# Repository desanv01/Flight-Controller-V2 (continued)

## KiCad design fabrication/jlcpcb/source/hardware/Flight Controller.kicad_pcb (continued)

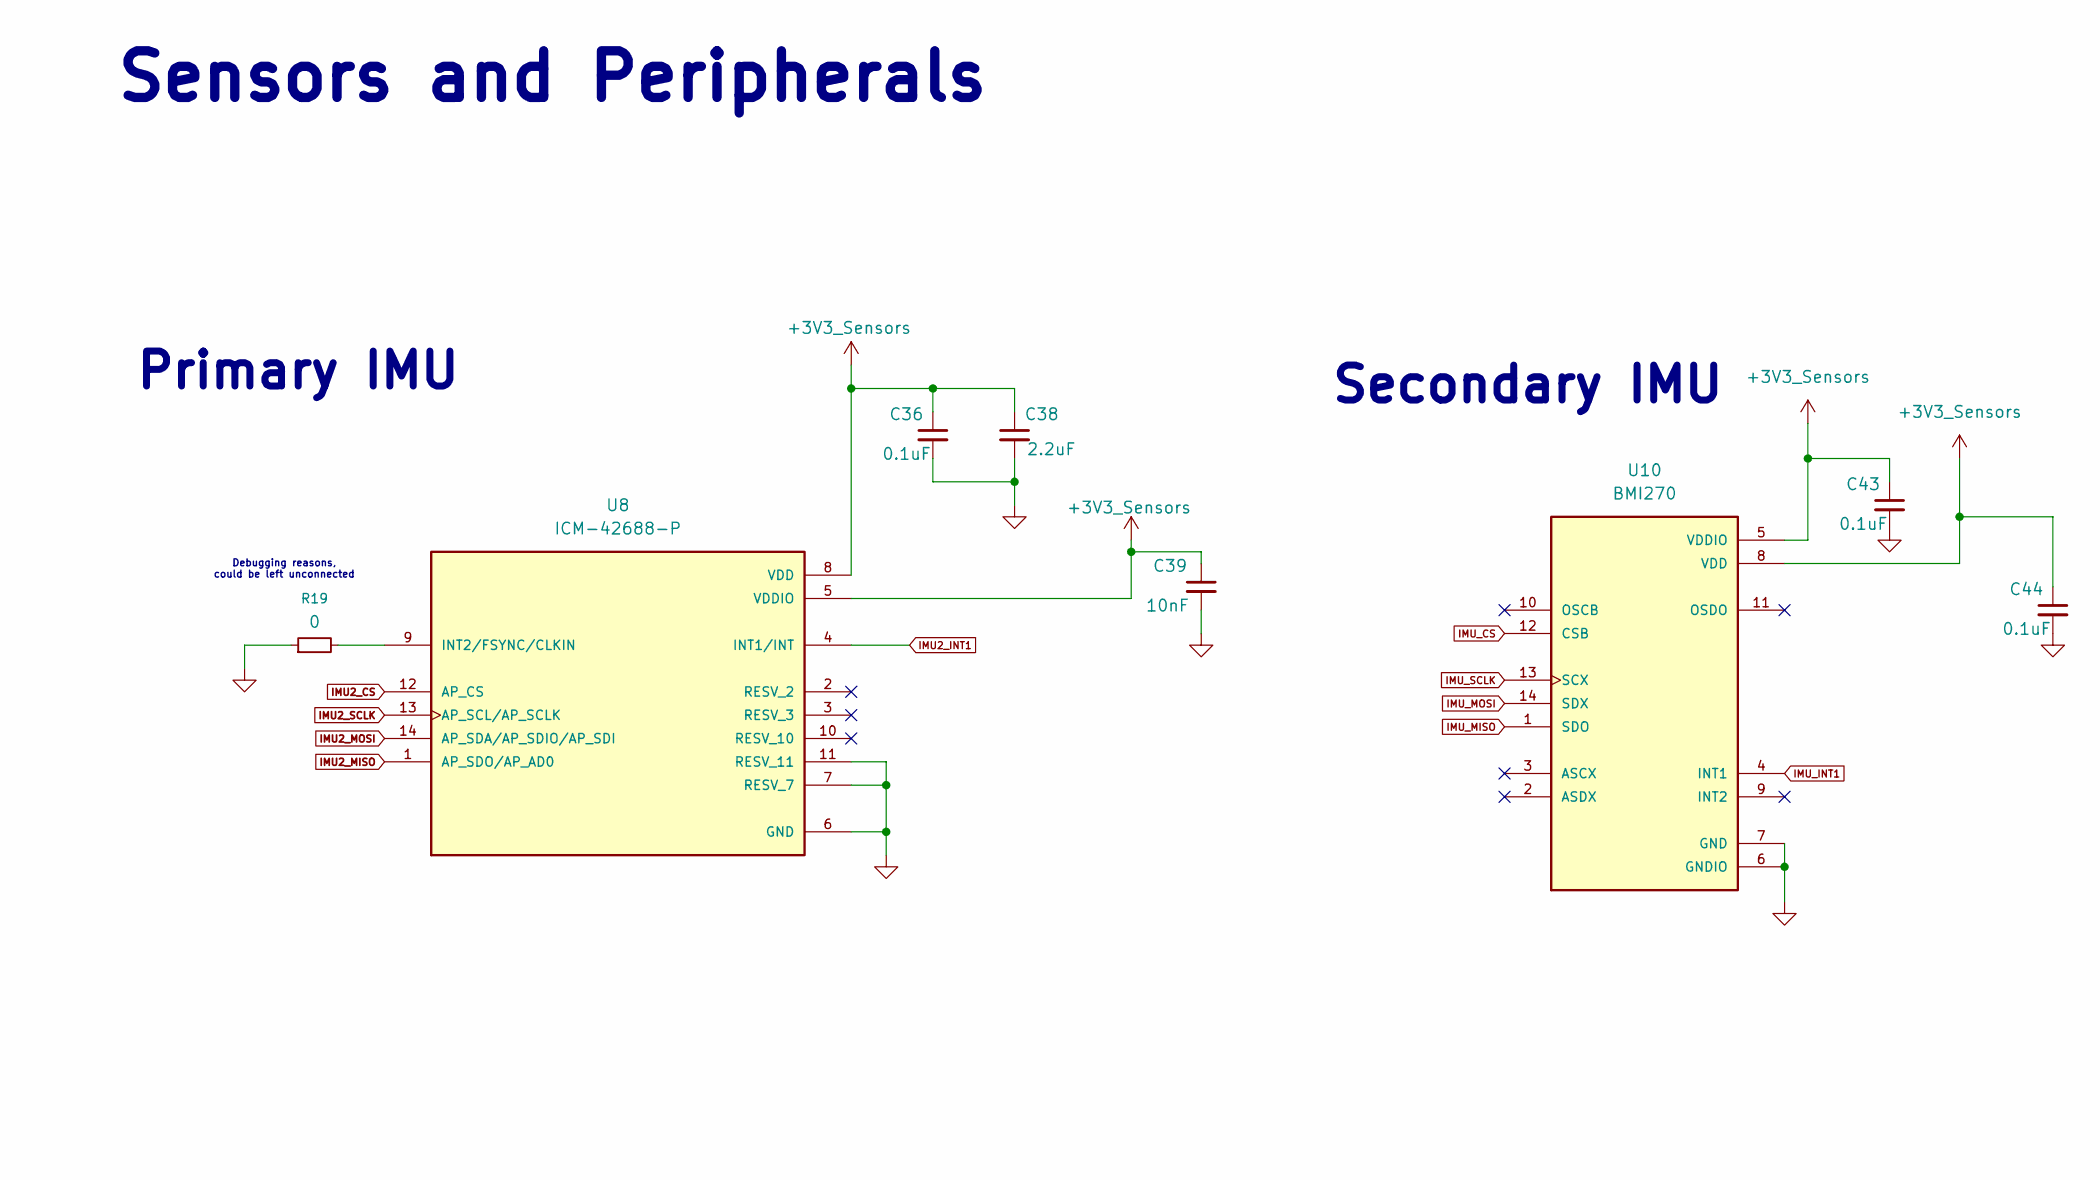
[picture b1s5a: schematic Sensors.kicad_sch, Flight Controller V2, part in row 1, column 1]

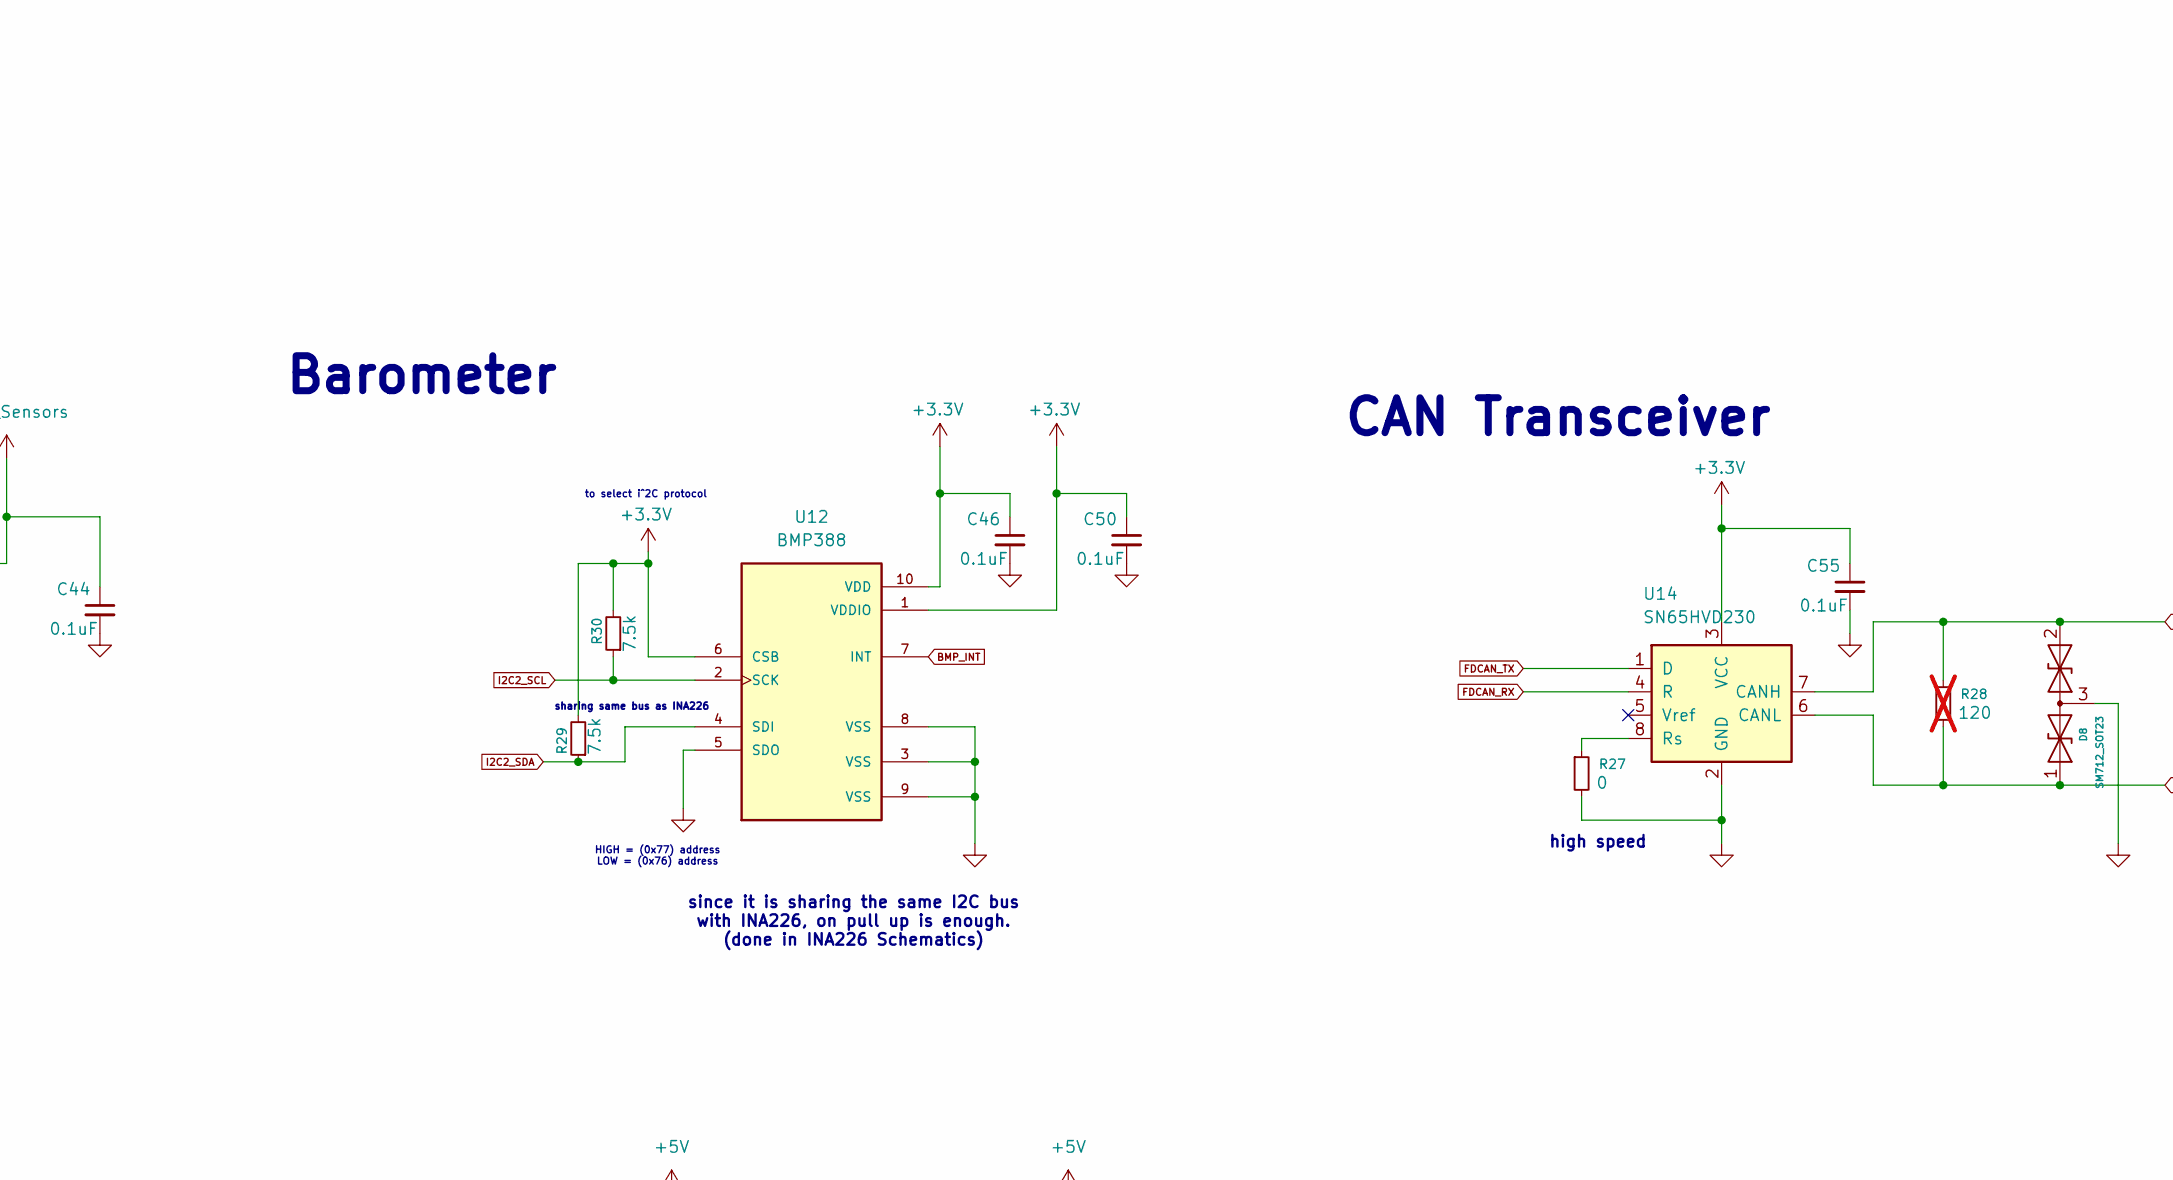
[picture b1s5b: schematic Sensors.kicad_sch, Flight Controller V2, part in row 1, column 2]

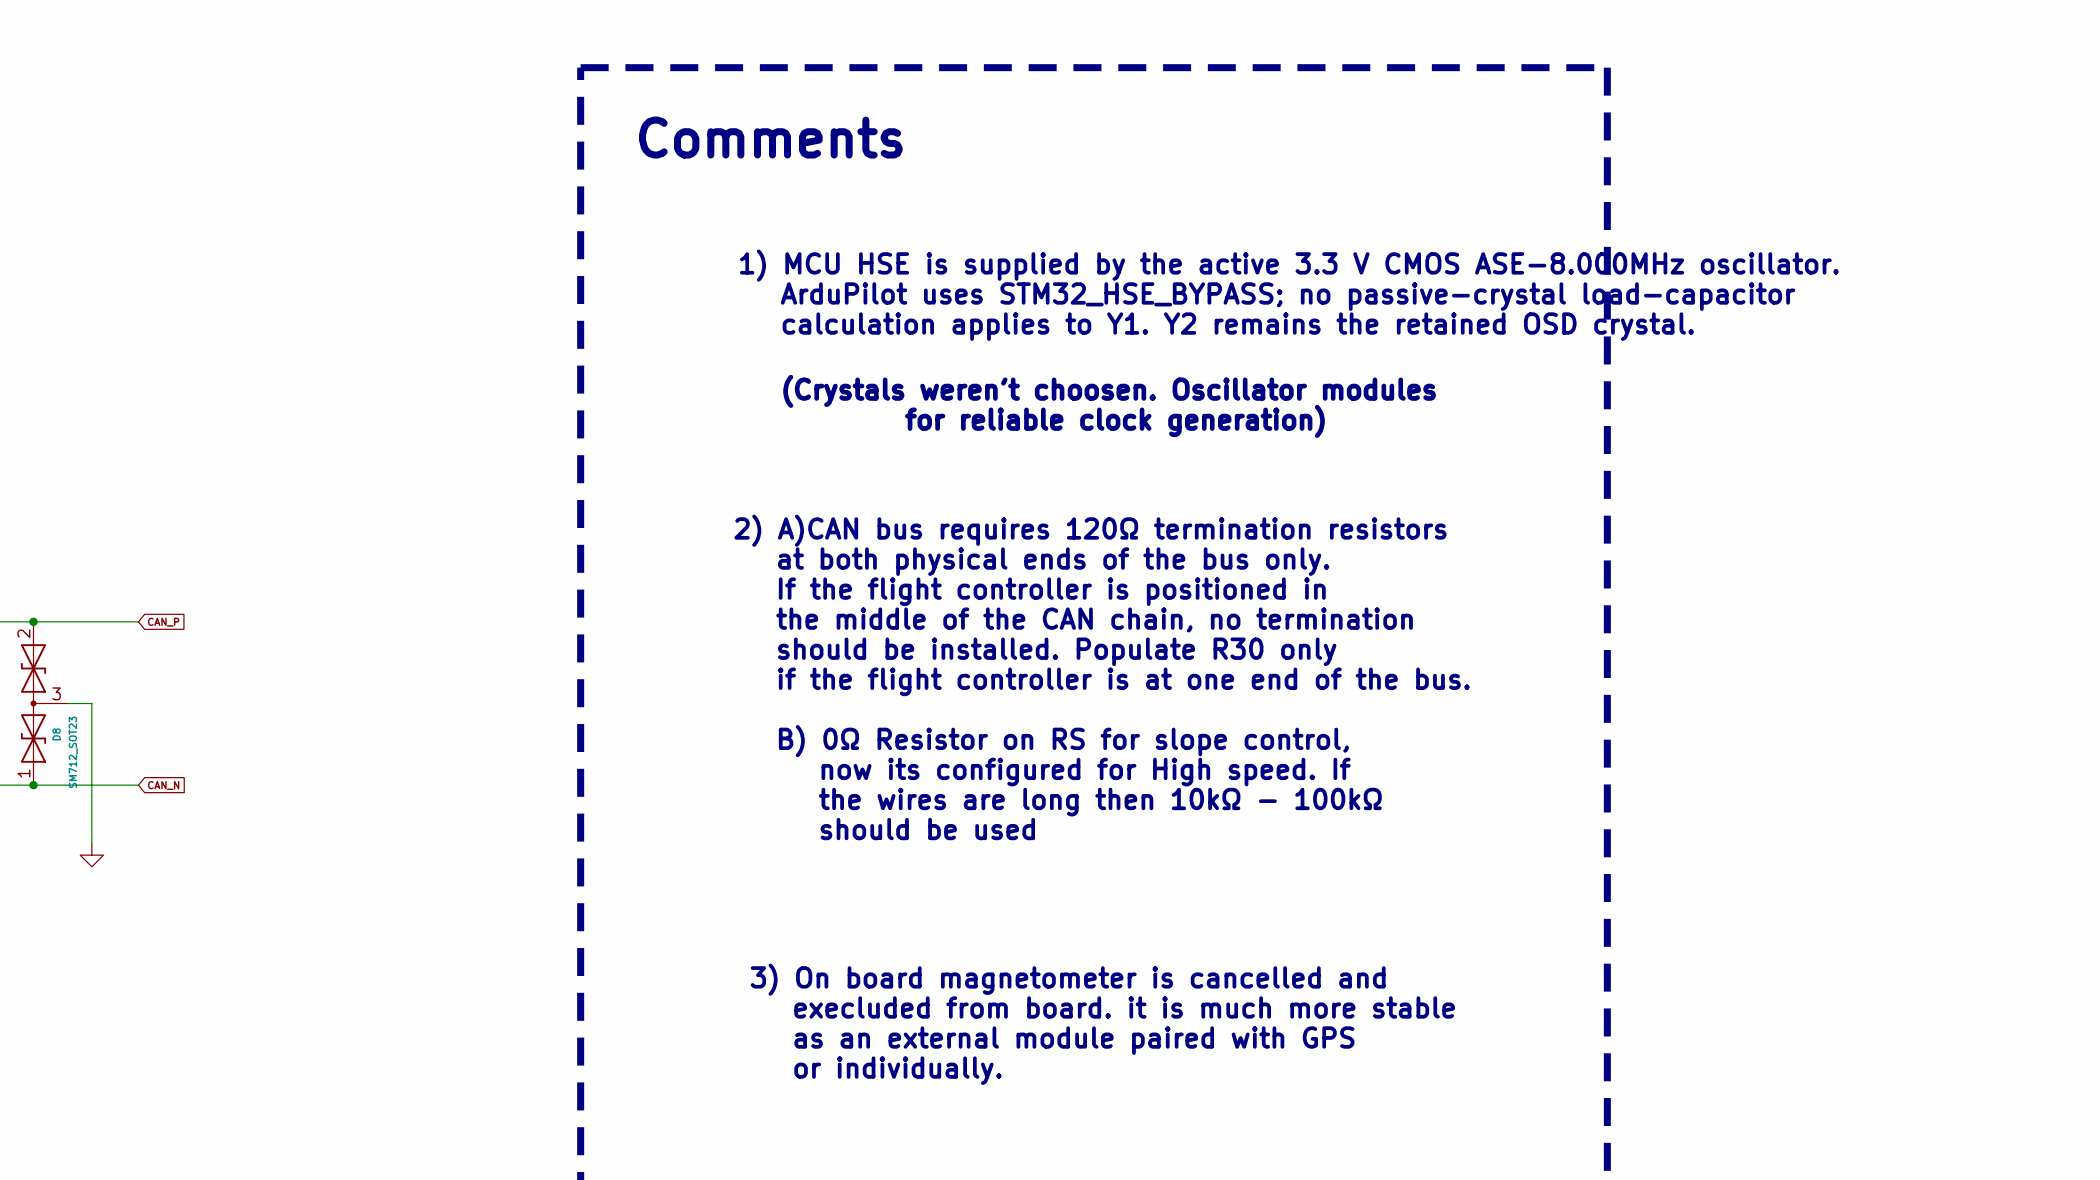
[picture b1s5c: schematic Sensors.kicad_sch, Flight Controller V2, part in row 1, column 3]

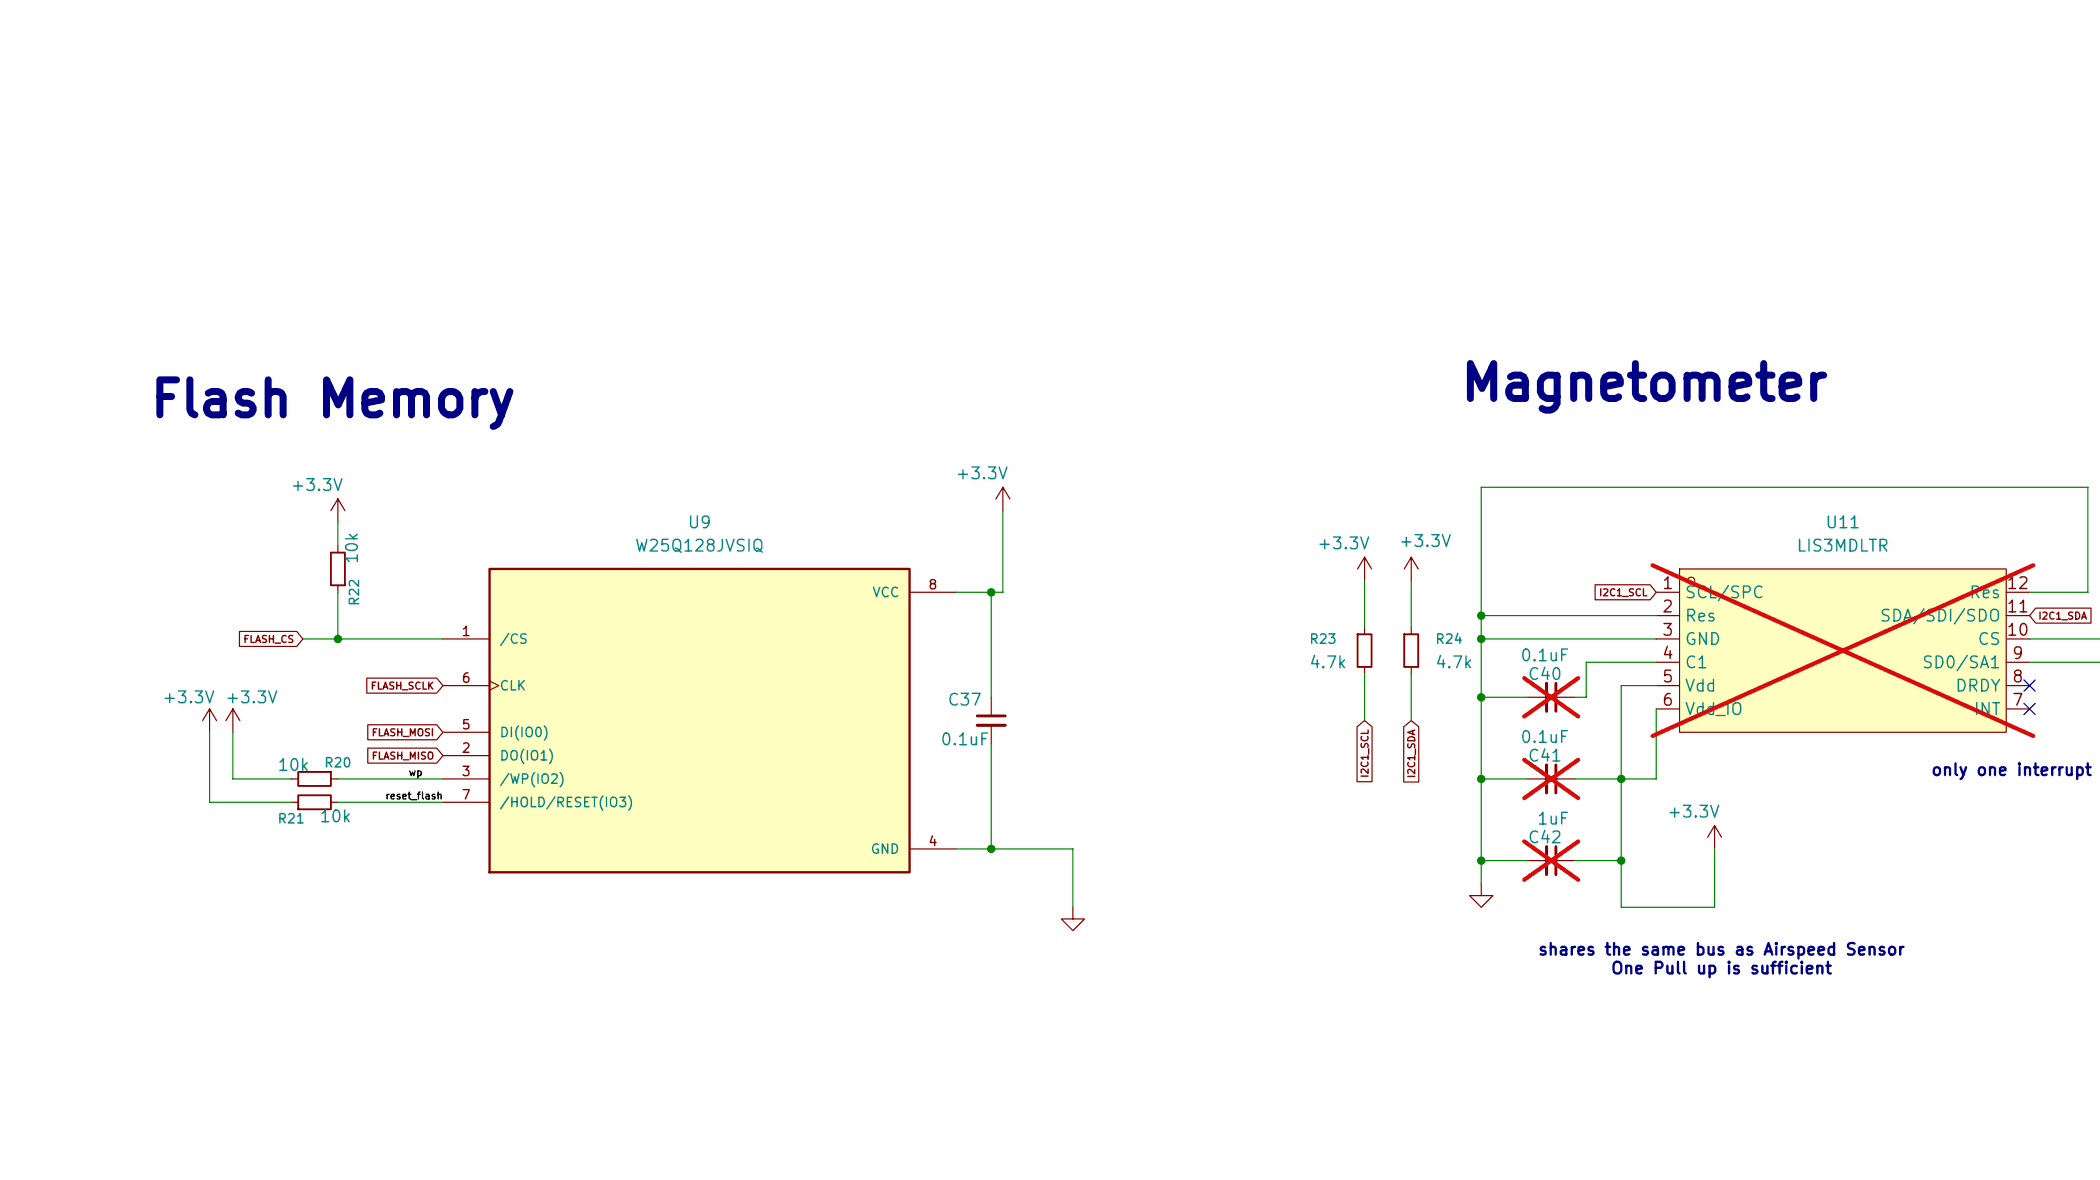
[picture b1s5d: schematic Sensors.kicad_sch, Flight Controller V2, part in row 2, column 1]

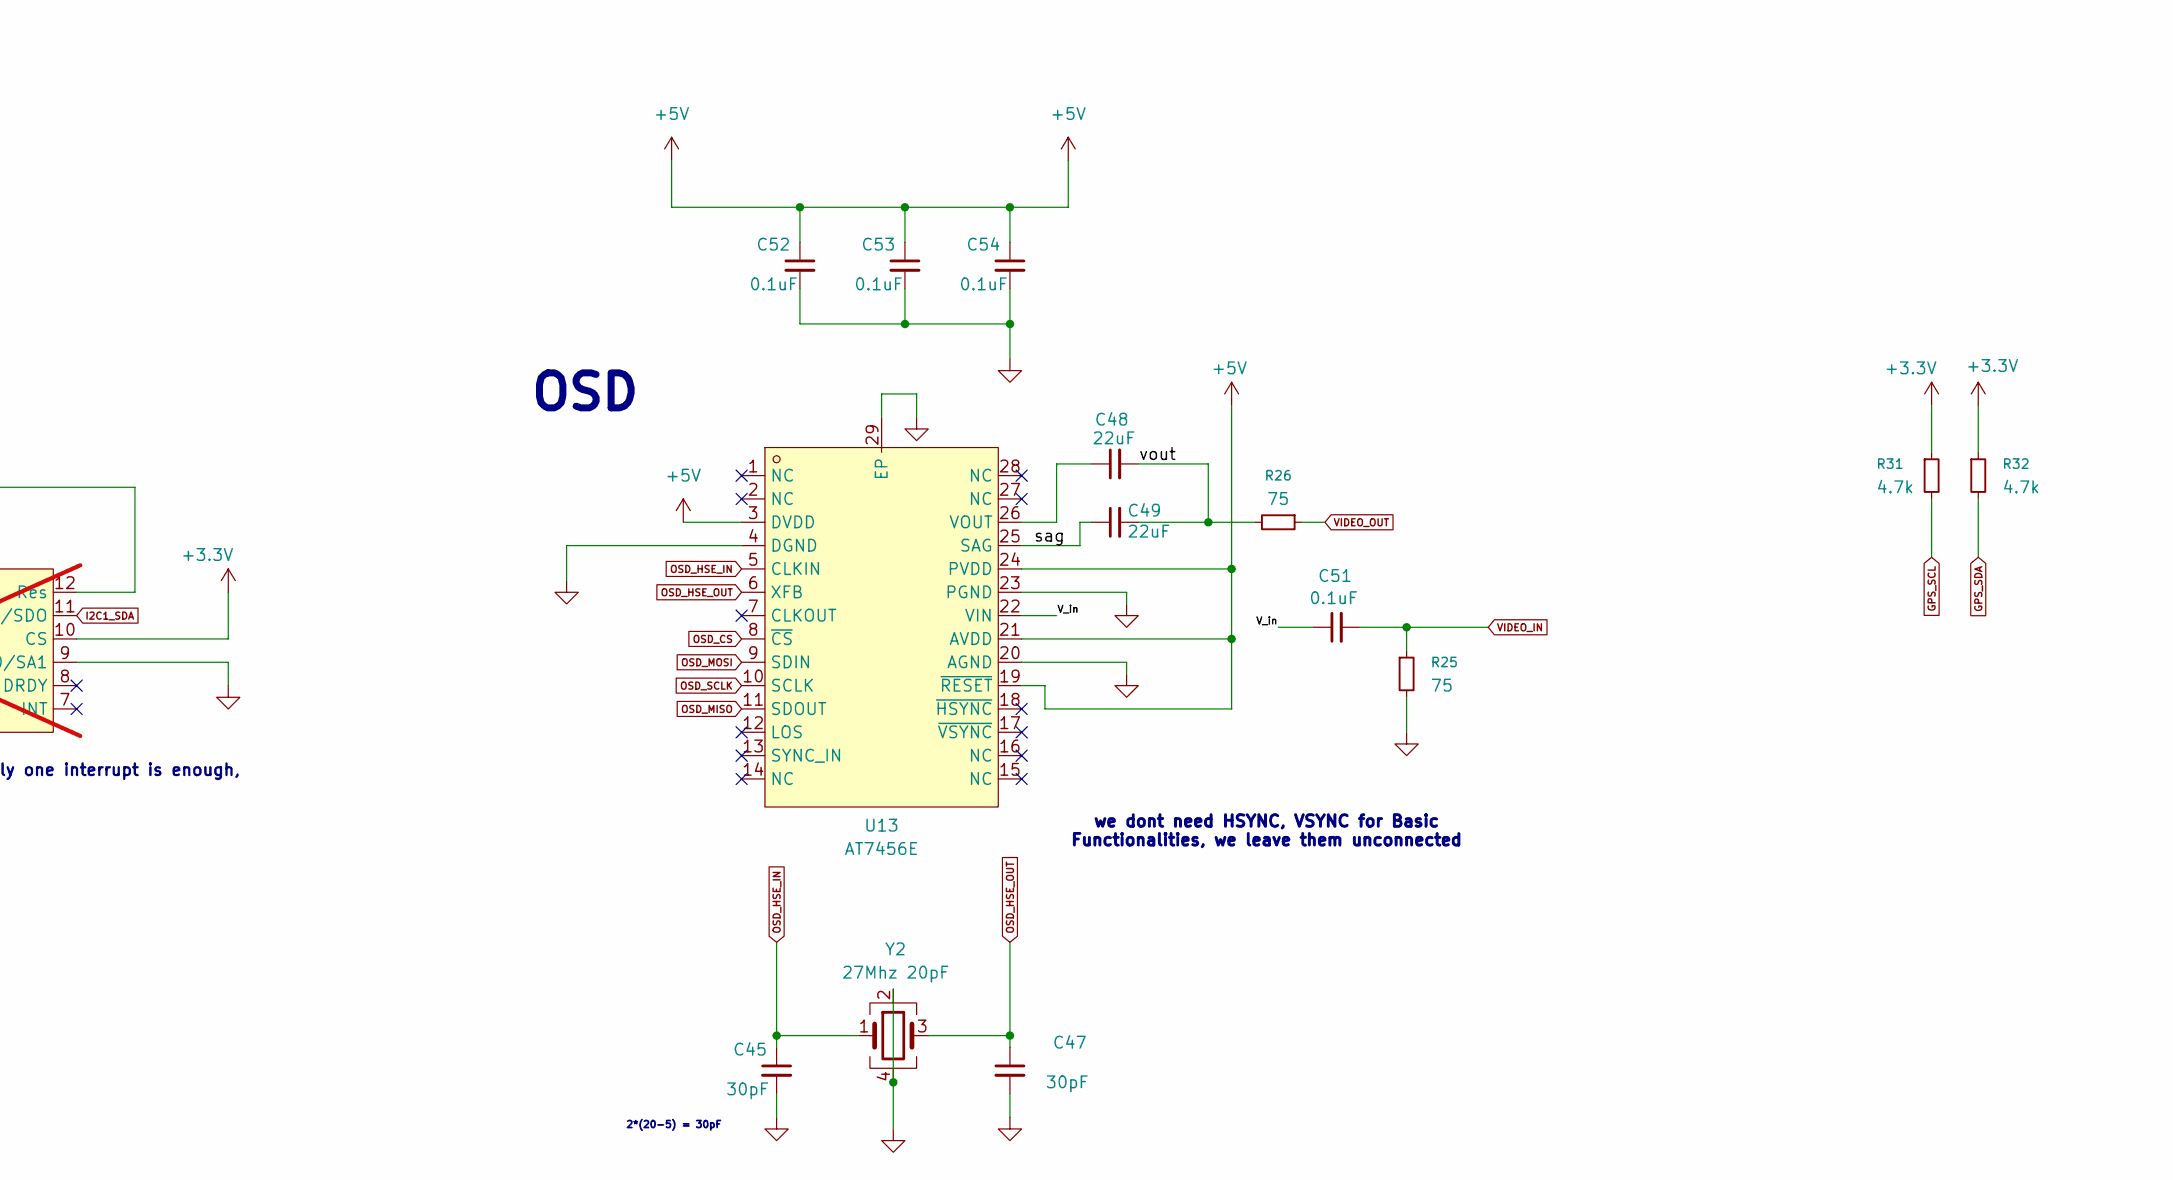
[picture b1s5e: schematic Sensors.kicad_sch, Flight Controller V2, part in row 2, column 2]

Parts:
C36, C37, C43, C44, C46, C50, C51, C52, C53, C54, C55: 0.1uF; C_0402_1005Metric
C38: 2.2uF; C_0603_1608Metric
C39: 10nF; C_0402_1005Metric
C40, C41: 0.1uF; C_0402_1005Metric; not fitted
C42: 1uF; C_0402_1005Metric; not fitted
C45, C47: 30pF; C_0402_1005Metric
C48, C49: 22uF; C_0603_1608Metric
D8: SM712_SOT23; SOT-23
R19, R27: 0; R_0402_1005Metric
R20, R21, R22: 10k; R_0402_1005Metric
R23, R24, R31, R32: 4.7k; R_0402_1005Metric
R25, R26: 75; R_0402_1005Metric
R28: 120; R_0402_1005Metric; not fitted
R29, R30: 7.5k; R_0402_1005Metric
U8: ICM-42688-P; PQFN50P300X250X97-14N; PARTREV 1.2
U9: W25Q128JVSIQ; PARTREV I
U10: BMI270; XDCR_BMI270
U11: LIS3MDLTR; (mag)LGA-12_L2.0-W2.0-P0.50-BL; LCSC Part C478483; not fitted
U12: BMP388; PQFN50P200X200X80-10N; PARTREV 1.1
U13: AT7456E; LCSC Part C82351
U14: SN65HVD230; SOIC-8_3.9x4.9mm_P1.27mm
Y2: 27Mhz 20pF; Crystal_SMD_3225-4Pin_3.2x2.5mm

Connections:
+3.3V: C37.1, C41.1, C42.1, C46.1, C50.1, C55.1, R20.2, R21.1, R22.2, R23.1, R24.1, R29.2, R30.2, R31.1, R32.1, U9.8 (VCC), U11.5 (Vdd), U11.6 (Vdd_IO), U11.10 (CS), U12.1 (VDDIO), U12.6 (CSB), U12.10 (VDD), U14.3 (VCC); also elsewhere on the board
+3V3_Sensors: C36.1, C38.1, C39.1, C43.1, C44.1, U8.5 (VDDIO), U8.8 (VDD), U10.5 (VDDIO), U10.8 (VDD); also elsewhere on the board
+5V: C52.1, C53.1, C54.1, U13.3 (DVDD), U13.19 (~RESET), U13.21 (AVDD), U13.24 (PVDD); also elsewhere on the board
/Sensors and Peripherals/V_in: C51.1, U13.22 (VIN)
/Sensors and Peripherals/reset_flash: R21.2, U9.7 (/HOLD/RESET(IO3))
/Sensors and Peripherals/sag: C49.1, U13.25 (SAG)
/Sensors and Peripherals/vout: C48.2, C49.2, R26.2
/Sensors and Peripherals/wp: R20.1, U9.3 (/WP(IO2))
BMP_INT: U12.7 (INT); also elsewhere on the board
CAN_N: D8.1 (A1), R28.2, U14.6 (CANL); also elsewhere on the board
CAN_P: D8.2 (A2), R28.1, U14.7 (CANH); also elsewhere on the board
FDCAN_RX: U14.4 (R); also elsewhere on the board
FDCAN_TX: U14.1 (D); also elsewhere on the board
FLASH_CS: R22.1, U9.1 (/CS); also elsewhere on the board
FLASH_MISO: U9.2 (DO(IO1)); also elsewhere on the board
FLASH_MOSI: U9.5 (DI(IO0)); also elsewhere on the board
FLASH_SCLK: U9.6 (CLK); also elsewhere on the board
GND: C36.2, C37.2, C38.2, C39.2, C40.2, C41.2, C42.2, C43.2, C44.2, C45.2, C46.2, C47.2, C50.2, C52.2, C53.2, C54.2, C55.2, D8.3 (common), R19.1, R25.2, R27.2, U8.6 (GND), U8.7 (RESV_7), U8.11 (RESV_11), U9.4 (GND), U10.6 (GNDIO), U10.7 (GND), U11.2 (Res), U11.3 (GND), U11.9 (SD0/SA1), U11.12 (Res), U12.3 (VSS), U12.5 (SDO), U12.8 (VSS), U12.9 (VSS), U13.4 (DGND), U13.20 (AGND), U13.23 (PGND), U13.29 (EP), U14.2 (GND), Y2.2, Y2.4; also elsewhere on the board
GPS_SCL: R31.2; also elsewhere on the board
GPS_SDA: R32.2; also elsewhere on the board
I2C1_SCL: R23.2, U11.1 (SCL/SPC); also elsewhere on the board
I2C1_SDA: R24.2, U11.11 (SDA/SDI/SDO); also elsewhere on the board
I2C2_SCL: R30.1, U12.2 (SCK); also elsewhere on the board
I2C2_SDA: R29.1, U12.4 (SDI); also elsewhere on the board
IMU2_CS: U8.12 (AP_CS); also elsewhere on the board
IMU2_INT1: U8.4 (INT1/INT); also elsewhere on the board
IMU2_MISO: U8.1 (AP_SDO/AP_AD0); also elsewhere on the board
IMU2_MOSI: U8.14 (AP_SDA/AP_SDIO/AP_SDI); also elsewhere on the board
IMU2_SCLK: U8.13 (AP_SCL/AP_SCLK); also elsewhere on the board
IMU_CS: U10.12 (CSB); also elsewhere on the board
IMU_INT1: U10.4 (INT1); also elsewhere on the board
IMU_MISO: U10.1 (SDO); also elsewhere on the board
IMU_MOSI: U10.14 (SDX); also elsewhere on the board
IMU_SCLK: U10.13 (SCX); also elsewhere on the board
unnamed: C40.1, U11.4 (C1)
unnamed: R19.2, U8.9 (INT2/FSYNC/CLKIN)
unnamed: C48.1, U13.26 (VOUT)
unnamed: R27.1, U14.8 (Rs)
OSD_CS: U13.8 (~CS); also elsewhere on the board
OSD_HSE_IN: C45.1, U13.5 (CLKIN), Y2.1
OSD_HSE_OUT: C47.1, U13.6 (XFB), Y2.3
OSD_MISO: U13.11 (SDOUT); also elsewhere on the board
OSD_MOSI: U13.9 (SDIN); also elsewhere on the board
OSD_SCLK: U13.10 (SCLK); also elsewhere on the board
VIDEO_IN: C51.2, R25.1; also elsewhere on the board
VIDEO_OUT: R26.1; also elsewhere on the board

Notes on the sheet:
Debugging reasons, could be left unconnected
shares the same bus as Airspeed Sensor One Pull up is sufficient
high speed
we dont need HSYNC, VSYNC for Basic Functionalities, we leave them unconnected
sharing same bus as INA226
(Crystals weren't choosen. Oscillator modules for reliable clock generation)
2*(20-5) = 30pF
1) MCU HSE is supplied by the active 3.3 V CMOS ASE-8.000MHz oscillator. ArduPilot uses STM32_HSE_BYPASS; no passive-crystal load-capacitor calculation applies to Y1. Y2 remains the retained OSD crystal.
HIGH = (0x77) address LOW = (0x76) address
to select i^2C protocol
only one interrupt is enough,
Magnetometer
2) A)CAN bus requires 120Ω termination resistors at both physical ends of the bus only. If the flight controller is positioned in the middle of the CAN chain, no termination should be installed. Populate R30 only if the flight controller is at one end of the bus. B) 0Ω Resistor on RS for slope cont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
Barometer
Flash Memory
3) On board magnetometer is cancelled and execluded from board. it is much more stable as an external module paired with GPS or individually.
OSD
Comments
Secondary IMU
Primary IMU
CAN Transceiver
Sensors and Peripherals
since it is sharing the same I2C bus with INA226, on pull up is enough. (done in INA226 Schematics)

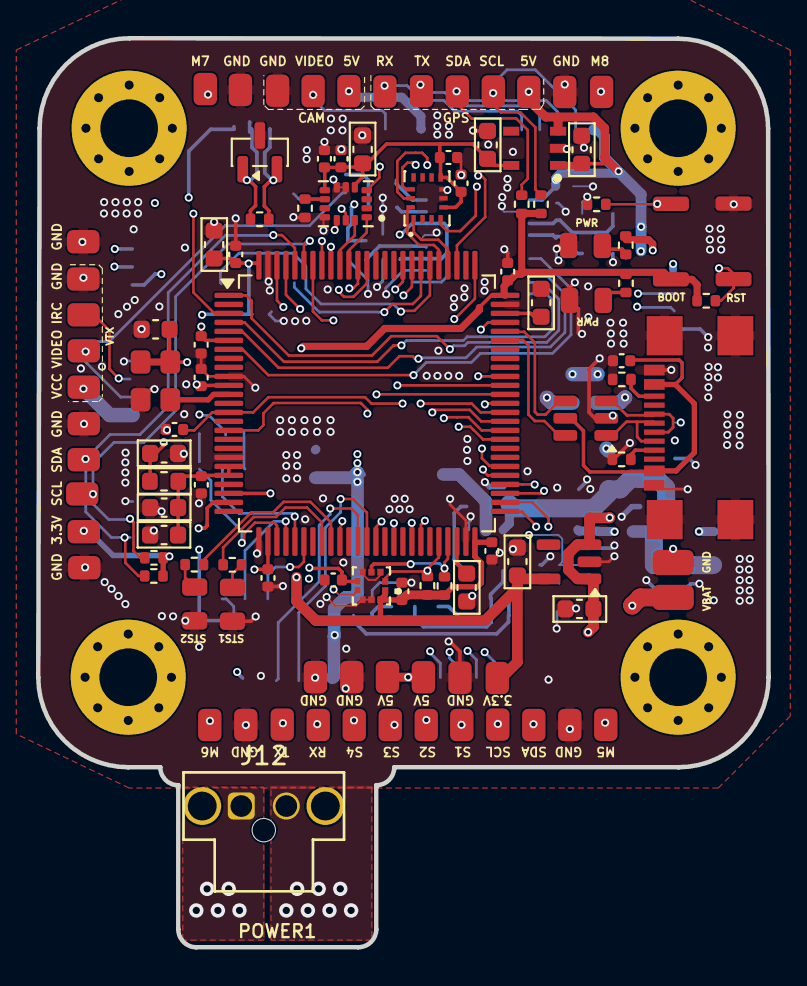
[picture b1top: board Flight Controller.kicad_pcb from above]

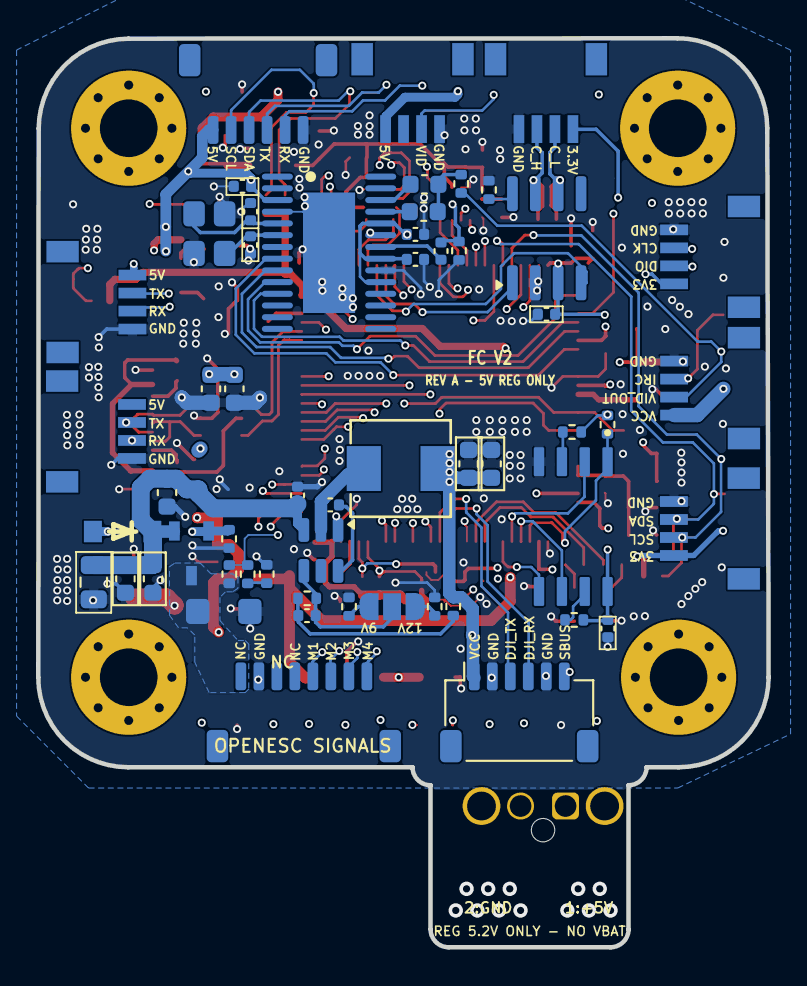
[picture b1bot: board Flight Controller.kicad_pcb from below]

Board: 6 copper layers, 40.6 x 50.5 mm, 162 parts (55 on the bottom side), 102 nets.

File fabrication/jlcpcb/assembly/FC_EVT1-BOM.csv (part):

"Designators","Value","Footprint","Datasheet","Description","Manufacturer","MPN","LCSC","MatingHousing","CrimpTerminal","TPA","Qty"
"C1,C3,C10","10uF","Capacitor_SMD:C_0603_1608Metric","","Unpolarized capacitor, small symbol","","","","","","","3"
"C2,C5,C24-C26,C28,C29,C31,C32,C36,C37,C43,C44,C46,C50-C55","0.1uF","Capacitor_SMD:C_0402_1005Metric","","Unpolarized capacitor, small symbol","","","","","","","20"
"C4","22uF","Capacitor_SMD:C_0805_2012Metric","","Unpolarized capacitor, small symbol","","","","","","","1"
"C6,C7,C15,C16,C48,C49","22uF","Capacitor_SMD:C_0603_1608Metric","","Unpolarized capacitor, small symbol","","","","","","","6"
"C8","75pF","Capacitor_SMD:C_0402_1005Metric","","Unpolarized capacitor, small symbol","","","","","","","1"
"C9","4.7uF","Capacitor_SMD:C_0402_1005Metric","","Unpolarized capacitor, small symbol","","","","","","","1"
"C17,C18,C20,C23,C27","1uF","Capacitor_SMD:C_0603_1608Metric","","Unpolarized capacitor, small symbol","","","","","","","5"
"C19,C22","4.7uF","Capacitor_SMD:C_0603_1608Metric","","Unpolarized capacitor, small symbol","","","","","","","2"
"C21","10nF","Capacitor_SMD:C_0603_1608Metric","","Unpolarized capacitor, small symbol","","","","","","","1"
"C30,C39","10nF","Capacitor_SMD:C_0402_1005Metric","","Unpolarized capacitor, small symbol","","","","","","","2"
"C33","0.1uF","Capacitor_SMD:C_0603_1608Metric","","Unpolarized capacitor, small symbol","","","","","","","1"
"C34,C35,C38","2.2uF","Capacitor_SMD:C_0603_1608Metric","","Unpolarized capacitor, small symbol","","","","","","","3"
"C45,C47","30pF","Capacitor_SMD:C_0402_1005Metric","","Unpolarized capacitor, small symbol","","","","","","","2"
"D1","SMF26A","Diode_SMD:D_SMF","https://www.vishay.com/doc?85881","200W unidirectional Transil Transient Voltage Suppressor, 26Vrwm, SMF","","","","","","","1"
"D2","BZT52C12-13-F","memo:(zener)SOD-123F_L2.8-W1.8-LS3.7-RD","https://lcsc.com/product-detail/Others_Diodes-Incorporated_B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","","","","","","","","1"
"D4-D7","LED","LED_SMD:LED_0805_2012Metric","","Light emitting diode","","","","","","","4"
"D8","SM712_SOT23","Package_TO_SOT_SMD:SOT-23","https://www.littelfuse.com/~/media/electronics/datasheets/tv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","7V/12V, 600W Asymmetrical TVS Diode Array, SOT-23","","","","","","","1"
"FB1","1k@100Mhz","Inductor_SMD:L_0603_1608Metric","","Ferrite bead, small symbol","","","","","","","1"
"H1-H4","MountingHole","MountingHole:MountingHole_3.2mm_M3_Pad_Via","","","","","","","","","4"
"J1","USB4110GFA","memo:GCT_USB4110GFA","","","","","","","","","1"
"J2","FPV","memo:CONN-SMD_4P-P1.00_SM04B-SRSS-TB-LF-SN","","","","","","","","","1"
"J3","ST_LINK","memo:CONN-SMD_4P-P1.00_SM04B-SRSS-TB-LF-SN","","Generic connector, single row, 01x04, script generated (kicad-library-utils/schlib/autogen/connector/)","","","","","","","1"
"J4","GPS","Connector_JST:JST_SH_SM06B-SRSS-TB_1x06-1MP_P1.00mm_Horizontal","","Generic connector, single row, 01x06, script generated (kicad-library-utils/schlib/autogen/connector/)","","","","","","","1"
"J5","Airspeed sensor","memo:CONN-SMD_4P-P1.00_SM04B-SRSS-TB-LF-SN","","","","","","","","","1"
"J6","OpenESC SIGNAL-ONLY","Connector_JST:JST_SH_SM08B-SRSS-TB_1x08-1MP_P1.00mm_Horizontal","","Generic connector, single row, 01x08, script generated (kicad-library-utils/schlib/autogen/connector/)","","","","","","","1"
"J7","RC Receiver","memo:CONN-SMD_4P-P1.00_SM04B-SRSS-TB-LF-SN","","Generic connector, single row, 01x04, script generated (kicad-library-utils/schlib/autogen/connector/)","","","","","","","1"
"J8","VTX","memo:CONN-SMD_4P-P1.00_SM04B-SRSS-TB-LF-SN","","","","","","","","","1"
"J9","DJI","Connector_JST:JST_SH_SM06B-SRSS-TB_1x06-1MP_P1.00mm_Horizontal","","Generic connector, single row, 01x06, script generated (kicad-library-utils/schlib/autogen/connector/)","","","","","","","1"
"J10","CAN BUS","memo:CONN-SMD_4P-P1.00_SM04B-SRSS-TB-LF-SN","","","","","","","","","1"
"J11","MAVLINK SIGNAL-ONLY","memo:CONN-SMD_4P-P1.00_SM04B-SRSS-TB-LF-SN","","","","","","","","","1"
"J12","POWER1 REGULATED 5.2V IN","FC_Footprints:Molex_Nano-Fit_105311-1202_1x02_P2.50mm_Vertical_SolderClip","https://www.molex.com/en-us/products/part-detail/1053111202","Nano-Fit 2.50 mm 2-circuit vertical top-entry solder-clip header; black; 0.38 um gold; pin 1 +5V, pin 2 GND","Molex","105311-1202","","105307-1202","105300-2200","105325-1002","1"
"L1","15uH","memo:IND-SMD_L5.4-W5.2","","Inductor, small symbol","","","","","","","1"
"Q1","AO3407A","memo:AO3407A","https://lcsc.com/product-detail/MOSFET_AOS_AO3407A_AO3407A_C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","","","","","","","","1"
"R1,R2","5.1k","Resistor_SMD:R_0402_1005Metric","","Resistor, small symbol","","","","","","","2"
"R3,R5","100k","Resistor_SMD:R_0402_1005Metric","","Resistor, small symbol","","","","","","","2"
"R4","49.9","Resistor_SMD:R_0402_1005Metric","","Resistor, small symbol","","","","","","","1"
"R5B1","7.15K","Resistor_SMD:R_0402_1005Metric","","Resistor, small symbol","","","","","","","1"
"R5C1","5.23k","Resistor_SMD:R_0402_1005Metric","","Resistor, small symbol","","","","","","","1"
"R6","4.42k","Resistor_SMD:R_0402_1005Metric","","Resistor, small symbol","","","","","","","1"
"R7","20k","Resistor_SMD:R_0402_1005Metric","","Resistor, small symbol","","","","","","","1"
"R8,R19,R27","0","Resistor_SMD:R_0402_1005Metric","","Resistor, small symbol","","","","","","","3"
"R13,R14,R17,R18","330","Resistor_SMD:R_0402_1005Metric","","Resistor, small symbol","","","","","","","4"
"R15,R16,R20-R22","10k","Resistor_SMD:R_0402_1005Metric","","Resistor, small symbol","","","","","","","5"
"R23,R24,R31,R32","4.7k","Resistor_SMD:R_0402_1005Metric","","Resistor, small symbol","","","","","","","4"
"R25,R26","75","Resistor_SMD:R_0402_1005Metric","","Resistor, small symbol","","","","","","","2"
"R29,R30","7.5k","Resistor_SMD:R_0402_1005Metric","","Resistor, small symbol","","","","","","","2"
"SW1","reset","Button_Switch_SMD:SW_Push_SPST_NO_Alps_SKRK","","Push button switch, generic, two pins","","","","","","","1"
"SW2","MCU_BOOT","Button_Switch_SMD:SW_Push_SPST_NO_Alps_SKRK","","Push button switch, generic, two pins","","","","","","","1"
"U1","TPS54302","Package_TO_SOT_SMD:SOT-23-6","http://www.ti.com/lit/ds/symlink/tps54302.pdf","3A, 4.5 to 28V Input, EMI Friendly integrated switch synchronous step-down regulator, pulse-skipping, SOT-23-6","","","","","","","1"
"U2","USBLC6-2SC6","Package_TO_SOT_SMD:SOT-23-6","https://www.st.com/resource/en/datasheet/usblc6-2.pdf","Very low capacitance ESD protection diode, 2 data-line, SOT-23-6","","","","","","","1"
"U5","AP2112K-3.3","Package_TO_SOT_SMD:SOT-23-5","https://www.diodes.com/assets/Datasheets/AP2112.pdf","600mA low dropout linear regulator, with enable pin, 3.8V-6V input voltage range, 3.3V fixed positive output, SOT-23-5","","","","","","","1"
"U6","AP7343-33W5-7","memo:(AP7343 )SOT-25_L3.0-W1.6-P0.95-LS2.8-BL","https://lcsc.com/product-detail/presales_Diodes-Incorporated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","","","","","","","","1"
"U7","STM32H743VITx","Package_QFP:LQFP-100_14x14mm_P0.5mm","https://www.st.com/resource/en/datasheet/stm32h743vi.pdf","STMicroelectronics Arm Cortex-M7 MCU, 2048KB flash, 1024KB RAM, 480 MHz, 1.71-3.6V, 82 GPIO, LQFP100","","","","","","","1"
"U8","ICM-42688-P","memo:PQFN50P300X250X97-14N","","","","","","","","","1"
"U9","W25Q128JVSIQ","memo:W25Q128JVSIQ","","","","","","","","","1"
"U10","BMI270","memo:XDCR_BMI270","","","","","","","","","1"
"U12","BMP388","memo:PQFN50P200X200X80-10N","","","","","","","","","1"
"U13","AT7456E","memo:AT7456E","https://lcsc.com/product-detail/Analog-ICs_AT7456E_C82351.html","","","","","","","","1"
"U14","SN65HVD230","Package_SO:SOIC-8_3.9x4.9mm_P1.27mm","http://www.ti.com/lit/ds/symlink/sn65hvd230.pdf","CAN Bus Transceivers, 3.3V, 1Mbps, Low-Power capabilities, SOIC-8","","","","","","","1"
"Y1","ASE-8.000MHZ-LC-T","Oscillator:Oscillator_SMD_Abracon_ASE-4Pin_3.2x2.5mm","http://www.abracon.com/Oscillators/ASV.pdf","3.3V CMOS SMD Crystal Clock Oscillator, Abracon","","","","","","","1"
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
